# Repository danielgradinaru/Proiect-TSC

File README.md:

# eBook Reader

Proiect hardware complet pentru un eBook Reader portabil, cu consum redus de energie, afisaj E-Paper si conectivitate moderna, proiectat in jurul microcontrollerului ESP32-C6-WROOM-1-N8.

# Arhitectura Hardware

## Microcontroller

### ESP32-C6-WROOM-1-N8
- Core RISC-V
- Conectivitate: Wi-Fi 6, Bluetooth 5
- Criptografie hardware
- [Specificații oficiale](https://www.espressif.com/en/products/modules/esp32-c6)

### Memorie Flash externă
- **W25Q512JVEIQ** – 64MB, conectată prin SPI

### Interfețe disponibile
- I2C, SPI și GPIO dedicate componentelor externe

---

## Alimentare

### USB-C (PMF0501)
- Intrare de 5V din surse standard

### Protecție ESD (USBLC6-2SC6Y)
- Protecție bidirecțională pentru liniile USB

### Încărcător Li-Po (MCP73831)
- Circuit simplu de încărcare pentru o celulă Li-Po (max. 500mA)

### Baterie
- Li-Po 3.7V

### Regulator LDO (MCP1700-3302E)
- Reglează tensiunea la 3.3V pentru alimentarea majorității componentelor

---

## Afișaj E-Ink

### Conector MP1
- Compatibil cu ecrane E-Ink de 1.54", 200x200px

### Circuit de alimentare pentru afișaj
- Componente: Q3 (tranzistor), L1 (inductor), D2 (diodă)
- Rol: generare tensiune specifică pentru EPD

### Selector tip display (SJ1)
- Jumpere pentru alegerea tipului de ecran

### Interfață
- SPI + GPIO, conectat direct la ESP32-C6

---

## Memorie Externă

- **Card SD (U4)** – pentru stocarea fișierelor eBook (conectat prin SPI)
- **64MB NOR Flash (W25Q512JVEIQ)** – memorie extinsă pentru firmware, fonturi, imagini (conectată pe SPI dedicat)

---

## Senzori și Periferice

### BME688
- Senzor pentru temperatură, umiditate, presiune și compuși volatili (VOCs)
- Comunicație: I2C

### RTC – DS3231SN
- Modul de timp real de înaltă precizie
- Comunicație: I2C

### MAX17048G-T10
- Fuel gauge pentru monitorizarea nivelului bateriei
- Comunicație: I2C

### Butoane (BD5229)
- Butoane Reset și Boot
- Conectate pe pini GPIO configurabili

### Qwiic / Stemma QT (J5)
- Conector pentru extensii rapide I2C

---

## Conexiuni ESP32-C6 (pini utilizati)

| Componenta     | Interfata  | Pini ESP32-C6                      | Observatii                    |
|----------------|------------|------------------------------------|-------------------------------|
| SD Card        | SPI        | GPIO10, GPIO11, GPIO12, GPIO13     | Bus SPI pentru card SD        |
| NOR Flash      | SPI        | GPIO6, GPIO7, GPIO8, GPIO9         | Bus SPI separat               |
| E-Ink Display  | SPI + GPIO | GPIO18, GPIO19, GPIO20, GPIO21     | Control display si date       |
| BME688         | I2C        | GPIO1 (SDA), GPIO2 (SCL)           | Bus comun I2C                 |
| DS3231         | I2C        | GPIO1 (SDA), GPIO2 (SCL)           | Comun cu ceilalti senzori     |
| MAX17048       | I2C        | GPIO1 (SDA), GPIO2 (SCL)           | Comun cu ceilalti senzori     |
| Butoane        | GPIO       | GPIO0 (RST), GPIO3 (BOOT)          | Control de sistem             |
| Test Pads      | GPIO/UART  | GPIO17, GPIO22                     | Debug                         |
| Stemma/Qwiic   | I2C        | GPIO1 (SDA), GPIO2 (SCL)           | Extensii rapide               |

---

## Estimare consum de energie

| Modul                  | Consum mediu        |
|------------------------|---------------------|
| ESP32-C6 activ         | ~80-100 mA          |
| ESP32-C6 deep sleep    | ~10 uA              |
| E-Ink refresh          | ~25 mA (temporar)   |
| SD Card (idle/acces)   | ~2 mA / ~50 mA      |
| RTC + BME688 standby   | ~3-5 uA             |
| MAX17048               | ~3 uA               |

**Durata estimata cu baterie 500mAh:**

- Utilizare medie: ~15-20 ore
- Standby (deep sleep): pana la cateva saptamani

---

## Informatii suplimentare

### Structura hardware
- Utilizare medie: ~15-20 ore
- Standby (deep sleep): pana la cateva saptamani

- PCB proiectat cu atentie la separarea blocurilor: alimentare, MCU, afisaj, senzori
- Plan de masa comun, trasee protejate si optimizate
- Mufe si conectori accesibili extern (USB, butoane, afisaj)

### Randari 3D si carcasa

- Randari disponibile cu componentele plasate
- Proiect finalizat atat din punct de vedere al carcasei 3D cat si al PCB
- Dimensiuni compacte si aspect ergonomic

## Aplicatii posibile

- eBook Reader offline
- Afisaj pentru date locale (calendar, vreme)

## Bill of Materials

| Name          | Reference                                                                      | Technical Sheet                                                                                                                                                                       | Model Link                                                                                                             |
|:--------------|:-------------------------------------------------------------------------------|:--------------------------------------------------------------------------------------------------------------------------------------------------------------------------------------|:-----------------------------------------------------------------------------------------------------------------------|
| BOOT_BUTTON   | BUTTON_CUSYOMV1                                                                | [Datasheet](https://industry.panasonic.com/global/en/downloads?tab=catalog&small_g_cd=203&part_no=EVQPUJ02K)                                                                          | [3D Model](https://industry.panasonic.com/global/en/products/control/switch/light-touch/number/evqpuj02k)              |
| C1            | ESP32_WROVER_EAGLE-LTSPICE_CC0402                                              | [Datasheet](https://componentsearchengine.com/Datasheets/2/CC0402MRX5R5BB106.pdf)                                                                                                     | [3D Model](https://componentsearchengine.com/part-view/CC0402MRX5R5BB106/YAGEO)                                        |
| C1_BAT        | ESP32_WROVER_EAGLE-LTSPICE_CC0402                                              | [Datasheet](https://componentsearchengine.com/Datasheets/2/CC0402MRX5R5BB106.pdf)                                                                                                     | [3D Model](https://componentsearchengine.com/part-view/CC0402MRX5R5BB106/YAGEO)                                        |
| C1_BAT1       | EAGLE-LTSPICE_CC0402                                                           | [Datasheet](https://s3.amazonaws.com/snapeda/datasheet/CC0402DRNPO9BN5R1_Yageo.pdf)                                                                                                   | [3D Model](https://www.snapeda.com/parts/CC0402DRNPO9BN5R1/Yageo/view-part/?ref=dk&t=LTSPICE_CC0402&con_ref=None)      |
| C2_BAT1       | EAGLE-LTSPICE_CC0402                                                           | [Datasheet](https://s3.amazonaws.com/snapeda/datasheet/CC0402DRNPO9BN5R1_Yageo.pdf)                                                                                                   | [3D Model](https://www.snapeda.com/parts/CC0402DRNPO9BN5R1/Yageo/view-part/?ref=dk&t=LTSPICE_CC0402&con_ref=None)      |
| C1_BAT2       | EAGLE-LTSPICE_CC0402                                                           | [Datasheet](https://s3.amazonaws.com/snapeda/datasheet/CC0402DRNPO9BN5R1_Yageo.pdf)                                                                                                   | [3D Model](https://www.snapeda.com/parts/CC0402DRNPO9BN5R1/Yageo/view-part/?ref=dk&t=LTSPICE_CC0402&con_ref=None)      |
| C2            | ESP32_WROVER_EAGLE-LTSPICE_CC0402                                              | [Datasheet](https://componentsearchengine.com/Datasheets/2/CC0402MRX5R5BB106.pdf)                                                                                                     | [3D Model](https://componentsearchengine.com/part-view/CC0402MRX5R5BB106/YAGEO)                                        |
| C2_BAT        | ESP32_WROVER_EAGLE-LTSPICE_CC0402                                              | [Datasheet](https://componentsearchengine.com/Datasheets/2/CC0402MRX5R5BB106.pdf)                                                                                                     | [3D Model](https://componentsearchengine.com/part-view/CC0402MRX5R5BB106/YAGEO)                                        |
| C3            | RCL_CPOL-EUCT3528                                                              | [Datasheet](https://s3.amazonaws.com/snapeda/datasheet/TAJB475K025RNJ_AVX.pdf)                                                                                                        | [3D Model](https://www.snapeda.com/parts/TAJB475K025RNJ/AVX/view-part/?ref=dk&t=capacitor%203528&con_ref=None)         |
| C4            | ESP32_WROVER_EAGLE-LTSPICE_CC0402                                              | [Datasheet](https://componentsearchengine.com/Datasheets/2/CC0402MRX5R5BB106.pdf)                                                                                                     | [3D Model](https://componentsearchengine.com/part-view/CC0402MRX5R5BB106/YAGEO)                                        |
| C4_USB        | ESP32_WROVER_EAGLE-LTSPICE_CC0402                                              | [Datasheet](https://componentsearchengine.com/Datasheets/2/CC0402MRX5R5BB106.pdf)                                                                                                     | [3D Model](https://componentsearchengine.com/part-view/CC0402MRX5R5BB106/YAGEO)                                        |
| C5            | ESP32_WROVER_EAGLE-LTSPICE_CC0402                                              | [Datasheet](https://componentsearchengine.com/Datasheets/2/CC0402MRX5R5BB106.pdf)                                                                                                     | [3D Model](https://componentsearchengine.com/part-view/CC0402MRX5R5BB106/YAGEO)                                        |
| C5_USB        | ESP32_WROVER_EAGLE-LTSPICE_CC0402                                              | [Datasheet](https://componentsearchengine.com/Datasheets/2/CC0402MRX5R5BB106.pdf)                                                                                                     | [3D Model](https://componentsearchengine.com/part-view/CC0402MRX5R5BB106/YAGEO)                                        |
| C6            | ESP32_WROVER_EAGLE-LTSPICE_CC0402                                              | [Datasheet](https://componentsearchengine.com/Datasheets/2/CC0402MRX5R5BB106.pdf)                                                                                                     | [3D Model](https://componentsearchengine.com/part-view/CC0402MRX5R5BB106/YAGEO)                                        |
| C7            | ESP32_WROVER_EAGLE-LTSPICE_CC0402                                              | [Datasheet](https://componentsearchengine.com/Datasheets/2/CC0402MRX5R5BB106.pdf)                                                                                                     | [3D Model](https://componentsearchengine.com/part-view/CC0402MRX5R5BB106/YAGEO)                                        |
| C8            | ESP32_WROVER_EAGLE-LTSPICE_CC0402                                              | [Datasheet](https://componentsearchengine.com/Datasheets/2/CC0402MRX5R5BB106.pdf)                                                                                                     | [3D Model](https://componentsearchengine.com/part-view/CC0402MRX5R5BB106/YAGEO)                                        |
| C9            | EAGLE-LTSPICE_CC0402                                                           | [Datasheet](https://s3.amazonaws.com/snapeda/datasheet/CC0402DRNPO9BN5R1_Yageo.pdf)                                                                                                   | [3D Model](https://www.snapeda.com/parts/CC0402DRNPO9BN5R1/Yageo/view-part/?ref=dk&t=LTSPICE_CC0402&con_ref=None)      |
| C10           | ESP32_WROVER_EAGLE-LTSPICE_CC0402                                              | [Datasheet](https://componentsearchengine.com/Datasheets/2/CC0402MRX5R5BB106.pdf)                                                                                                     | [3D Model](https://componentsearchengine.com/part-view/CC0402MRX5R5BB106/YAGEO)                                        |
| C10_SUPERCAP  | CPH3225A                                                                       | [Datasheet](https://www.snapeda.com/parts/CPH3225A/Seiko%20Instruments/datasheet/)                                                                                                    | [3D Model](https://www.snapeda.com/parts/CPH3225A/Seiko+Instruments/view-part/?ref=eda)                                |
| CHANGE_BUTTON | BUTTON_CUSYOMV1                                                                | [Datasheet](https://industry.panasonic.com/global/en/downloads?tab=catalog&small_g_cd=203&part_no=EVQPUJ02K)                                                                          | [3D Model](https://industry.panasonic.com/global/en/products/control/switch/light-touch/number/evqpuj02k)              |
| CHG_LED       | ADAFRUIT_LEDCHIP-LED0603                                                       | [Datasheet](https://www.snapeda.com/parts/KP-1608SURCK/Kingbright/datasheet/)                                                                                                         | [3D Model](https://www.snapeda.com/parts/KP-1608SURCK/Kingbright/view-part/?ref=search&t=LED%200603)                   |
| C_DELAY       | ESP32_WROVER_EAGLE-LTSPICE_CC0402                                              | [Datasheet](https://componentsearchengine.com/Datasheets/2/CC0402MRX5R5BB106.pdf)                                                                                                     | [3D Model](https://componentsearchengine.com/part-view/CC0402MRX5R5BB106/YAGEO)                                        |
| D1            | USBLC6-2SC6Y                                                                   | [Datasheet](https://www.snapeda.com/parts/USBLC6-2SC6Y/STMicroelectronics/datasheet/)                                                                                                 | [3D Model](https://www.snapeda.com/parts/USBLC6-2SC6Y/STMicroelectronics/view-part/?ref=snap)                          |
| D2            | ESP32_WROVER_AVX---SD0805S020S1R0_AVX_SD0805S020S1R0_0_0AVX_SD0805S020S1R0_0_0 | [Datasheet](http://datasheets.avx.com/schottky.pdf)                                                                                                                                   | [3D Model](https://ro.mouser.com/ProductDetail/KYOCERA-AVX/SD0805S020S1R0?qs=jCA%252BPfw4LHbpkAoSnwrdjw%3D%3D)         |
| D3            | MBR0530                                                                        | [Datasheet](https://www.snapeda.com/parts/MBR0530/ON%20Semiconductor/datasheet/)                                                                                                      | [3D Model](https://www.snapeda.com/parts/MBR0530/Onsemi/view-part/?ref=eda)                                            |
| D4            | MBR0530                                                                        | [Datasheet](https://www.snapeda.com/parts/MBR0530/ON%20Semiconductor/datasheet/)                                                                                                      | [3D Model](https://www.snapeda.com/parts/MBR0530/Onsemi/view-part/?ref=eda)                                            |
| D5            | MBR0530                                                                        | [Datasheet](https://www.snapeda.com/parts/MBR0530/ON%20Semiconductor/datasheet/)                                                                                                      | [3D Model](https://www.snapeda.com/parts/MBR0530/Onsemi/view-part/?ref=eda)                                            |
| D6            | PGB1010603MR                                                                   | [Datasheet](https://www.snapeda.com/parts/PGB1010603MR/Littelfuse%20Inc./datasheet/)                                                                                                  | [3D Model](https://www.snapeda.com/parts/PGB1010603MR/Littelfuse/view-part/?ref=eda)                                   |
| D7            | ESP32_WROVER_AVX---SD0805S020S1R0_AVX_SD0805S020S1R0_0_0AVX_SD0805S020S1R0_0_0 | [Datasheet](http://datasheets.avx.com/schottky.pdf)                                                                                                                                   | [3D Model](https://eu.mouser.com/ProductDetail/KYOCERA-AVX/SD0805S020S1R0?qs=jCA%252BPfw4LHbpkAoSnwrdjw%3D%3D)         |
| D8            | PGB1010603MR                                                                   | [Datasheet](https://www.snapeda.com/parts/PGB1010603MR/Littelfuse%20Inc./datasheet/)                                                                                                  | [3D Model](https://www.snapeda.com/parts/PGB1010603MR/Littelfuse/view-part/?ref=eda)                                   |
| D9            | PGB1010603MR                                                                   | [Datasheet](https://www.snapeda.com/parts/PGB1010603MR/Littelfuse%20Inc./datasheet/)                                                                                                  | [3D Model](https://www.snapeda.com/parts/PGB1010603MR/Littelfuse/view-part/?ref=eda)                                   |
| D10           | PGB1010603MR                                                                   | [Datasheet](https://www.snapeda.com/parts/PGB1010603MR/Littelfuse%20Inc./datasheet/)                                                                                                  | [3D Model](https://www.snapeda.com/parts/PGB1010603MR/Littelfuse/view-part/?ref=eda)                                   |
| D11           | PGB1010603MR                                                                   | [Datasheet](https://www.snapeda.com/parts/PGB1010603MR/Littelfuse%20Inc./datasheet/)                                                                                                  | [3D Model](https://www.snapeda.com/parts/PGB1010603MR/Littelfuse/view-part/?ref=eda)                                   |
| D12           | PGB1010603MR                                                                   | [Datasheet](https://www.snapeda.com/parts/PGB1010603MR/Littelfuse%20Inc./datasheet/)                                                                                                  | [3D Model](https://www.snapeda.com/parts/PGB1010603MR/Littelfuse/view-part/?ref=eda)                                   |
| EPD_C1        | ESP32_WROVER_EAGLE-LTSPICE_CC0402                                              | [Datasheet](https://componentsearchengine.com/Datasheets/2/CC0402MRX5R5BB106.pdf)                                                                                                     | [3D Model](https://componentsearchengine.com/part-view/CC0402MRX5R5BB106/YAGEO)                                        |
| EPD_C2        | ESP32_WROVER_EAGLE-LTSPICE_CC0402                                              | [Datasheet](https://componentsearchengine.com/Datasheets/2/CC0402MRX5R5BB106.pdf)                                                                                                     | [3D Model](https://componentsearchengine.com/part-view/CC0402MRX5R5BB106/YAGEO)                                        |
| EPD_C5        | ESP32_WROVER_EAGLE-LTSPICE_CC0402                                              | [Datasheet](https://componentsearchengine.com/Datasheets/2/CC0402MRX5R5BB106.pdf)                                                                                                     | [3D Model](https://componentsearchengine.com/part-view/CC0402MRX5R5BB106/YAGEO)                                        |
| EPD_C6        | ESP32_WROVER_EAGLE-LTSPICE_CC0402                                              | [Datasheet](https://componentsearchengine.com/Datasheets/2/CC0402MRX5R5BB106.pdf)                                                                                                     | [3D Model](https://componentsearchengine.com/part-view/CC0402MRX5R5BB106/YAGEO)                                        |
| EPD_C7        | ESP32_WROVER_EAGLE-LTSPICE_CC0402                                              | [Datasheet](https://componentsearchengine.com/Datasheets/2/CC0402MRX5R5BB106.pdf)                                                                                                     | [3D Model](https://componentsearchengine.com/part-view/CC0402MRX5R5BB106/YAGEO)                                        |
| EPD_C8        | ESP32_WROVER_EAGLE-LTSPICE_CC0402                                              | [Datasheet](https://componentsearchengine.com/Datasheets/2/CC0402MRX5R5BB106.pdf)                                                                                                     | [3D Model](https://componentsearchengine.com/part-view/CC0402MRX5R5BB106/YAGEO)                                        |
| EPD_C9        | ESP32_WROVER_EAGLE-LTSPICE_CC0402                                              | [Datasheet](https://componentsearchengine.com/Datasheets/2/CC0402MRX5R5BB106.pdf)                                                                                                     | [3D Model](https://componentsearchengine.com/part-view/CC0402MRX5R5BB106/YAGEO)                                        |
| EPD_C10       | ESP32_WROVER_EAGLE-LTSPICE_CC0402                                              | [Datasheet](https://componentsearchengine.com/Datasheets/2/CC0402MRX5R5BB106.pdf)                                                                                                     | [3D Model](https://componentsearchengine.com/part-view/CC0402MRX5R5BB106/YAGEO)                                        |
| EPD_C11       | ESP32_WROVER_EAGLE-LTSPICE_CC0402                                              | [Datasheet](https://componentsearchengine.com/Datasheets/2/CC0402MRX5R5BB106.pdf)                                                                                                     | [3D Model](https://componentsearchengine.com/part-view/CC0402MRX5R5BB106/YAGEO)                                        |
| EPD_C12       | ESP32_WROVER_EAGLE-LTSPICE_CC0402                                              | [Datasheet](https://componentsearchengine.com/Datasheets/2/CC0402MRX5R5BB106.pdf)                                                                                                     | [3D Model](https://componentsearchengine.com/part-view/CC0402MRX5R5BB106/YAGEO)                                        |
| IC1           | BD5229G-TR                                                                     | [Datasheet](https://datasheet.datasheetarchive.com/originals/distributors/Datasheets_SAMA/f2b9741ef86007909f138d561a359946.pdf)                                                       | [3D Model](https://componentsearchengine.com/part-view/BD5229G-TR/ROHM%20Semiconductor)                                |
| IC4           | XC6220A331MR-G                                                                 | [Datasheet](https://product.torexsemi.com/system/files/series/xc6220.pdf)                                                                                                             | [3D Model](https://componentsearchengine.com/part-view/XC6220A331MR-G/Torex)                                           |
| J1            | FH34SRJ-24S-0.5SH_99_                                                          | [Datasheet](https://www.hirose.com/en/product/document?clcode=CL0580-1255-6-99&productname=FH34SRJ-24S-0.5SH(99)&series=FH34SRJ&documenttype=2DDrawing&lang=en&documentid=0000990903) | [3D Model](https://componentsearchengine.com/part-view/FH34SRJ-24S-0.5SH(99)/Hirose)                                   |
| J2            | SAMACSYS_PARTS_USB4110-GF-A                                                    | [Datasheet](https://gct.co/files/drawings/usb4110.pdf)                                                                                                                                | [3D Model](https://componentsearchengine.com/part-view/USB4110-GF-A/GCT%20(GLOBAL%20CONNECTOR%20TECHNOLOGY))           |
| J3            | QWIIC_CONNECTORJS-1MM                                                          | [Datasheet](https://eu.mouser.com/ProductDetail/Adafruit/4208?qs=PzGy0jfpSMtbScLbr0L5dw%3D%3D)                                                                                        | [3D Model](https://grabcad.com/library/sparkfun-qwiic-right-angle-1)                                                   |
| J4            | 112A-TAAR-R03_ATTEND                                                           | [Datasheet](https://store.comet.srl.ro/Catalogue/Product/43497/)                                                                                                                      | [3D Model](https://store.comet.srl.ro/Catalogue/Product/43497/)                                                        |
| L1            | 744043680IND_4828-WE-TPC_WRE                                                   | [Datasheet](https://www.we-online.com/components/products/datasheet/744043680.pdf)                                                                                                    | [3D Model](https://ro.mouser.com/ProductDetail/Wurth-Elektronik/744043680?qs=PGXP4M47uW6VkZq%252BkzjrHA%3D%3D)         |
| PFMF.050.1    | ESP32C6_VARISTORCN1812                                                         | [Datasheet](https://www.mouser.co.uk/ProductDetail/EPCOS-TDK/B72520T0350K062?qs=dEfas%2FXlABIszF52uu7vrg%3D%3D)                                                                       | [3D Model](https://www.mouser.co.uk/ProductDetail/EPCOS-TDK/B72520T0350K062?qs=dEfas%2FXlABIszF52uu7vrg%3D%3D)         |
| Q1            | ESP32_WROVER_SPARKFUN-DISCRETESEMI_MOSFET_PCH-DMG2305UX-7                      | [Datasheet](https://www.diodes.com//assets/Datasheets/DMG2305UX.pdf)                                                                                                                  | [3D Model](https://componentsearchengine.com/part-view/DMG2305UX-7/Diodes%20Incorporated)                              |
| Q2            | ESP32_WROVER_SPARKFUN-DISCRETESEMI_MOSFET_PCH-DMG2305UX-7                      | [Datasheet](https://www.diodes.com//assets/Datasheets/DMG2305UX.pdf)                                                                                                                  | [3D Model](https://componentsearchengine.com/part-view/DMG2305UX-7/Diodes%20Incorporated)                              |
| Q3            | D8                                                                             | [Datasheet](https://componentsearchengine.com/Datasheets/1/SI1308EDL-T1-GE3.pdf)                                                                                                      | [3D Model](https://componentsearchengine.com/part-view/SI1308EDL-T1-GE3/Vishay)                                        |
| R1            | ESP32_WROVER_EAGLE-LTSPICE_RR0402                                              | [Datasheet](https://www.yageo.com/upload/media/product/products/datasheet/rchip/PYu-RC_Group_51_RoHS_L_12.pdf)                                                                        | [3D Model](https://componentsearchengine.com/part-view/R0402%201%25%20100%20K%20(RC0402FR-07100KL)/YAGEO)              |
| R1-PINH       | ESP32_WROVER_EAGLE-LTSPICE_RR0402                                              | [Datasheet](https://www.yageo.com/upload/media/product/products/datasheet/rchip/PYu-RC_Group_51_RoHS_L_12.pdf)                                                                        | [3D Model](https://componentsearchengine.com/part-view/R0402%201%25%20100%20K%20(RC0402FR-07100KL)/YAGEO)              |
| R1-PINH1      | ESP32_WROVER_EAGLE-LTSPICE_RR0402                                              | [Datasheet](https://www.yageo.com/upload/media/product/products/datasheet/rchip/PYu-RC_Group_51_RoHS_L_12.pdf)                                                                        | [3D Model](https://componentsearchengine.com/part-view/R0402%201%25%20100%20K%20(RC0402FR-07100KL)/YAGEO)              |
| R1_BAT        | ESP32_WROVER_EAGLE-LTSPICE_RR0402                                              | [Datasheet](https://www.yageo.com/upload/media/product/products/datasheet/rchip/PYu-RC_Group_51_RoHS_L_12.pdf)                                                                        | [3D Model](https://componentsearchengine.com/part-view/R0402%201%25%20100%20K%20(RC0402FR-07100KL)/YAGEO)              |
| R1_PWRUSB     | ESP32_WROVER_EAGLE-LTSPICE_RR0402                                              | [Datasheet](https://www.yageo.com/upload/media/product/products/datasheet/rchip/PYu-RC_Group_51_RoHS_L_12.pdf)                                                                        | [3D Model](https://componentsearchengine.com/part-view/R0402%201%25%20100%20K%20(RC0402FR-07100KL)/YAGEO)              |
| R2            | ESP32_WROVER_EAGLE-LTSPICE_RR0402                                              | [Datasheet](https://www.yageo.com/upload/media/product/products/datasheet/rchip/PYu-RC_Group_51_RoHS_L_12.pdf)                                                                        | [3D Model](https://componentsearchengine.com/part-view/R0402%201%25%20100%20K%20(RC0402FR-07100KL)/YAGEO)              |
| R2-PINH       | ESP32_WROVER_EAGLE-LTSPICE_RR0402                                              | [Datasheet](https://www.yageo.com/upload/media/product/products/datasheet/rchip/PYu-RC_Group_51_RoHS_L_12.pdf)                                                                        | [3D Model](https://componentsearchengine.com/part-view/R0402%201%25%20100%20K%20(RC0402FR-07100KL)/YAGEO)              |
| R2-PINH1      | ESP32_WROVER_EAGLE-LTSPICE_RR0402                                              | [Datasheet](https://www.yageo.com/upload/media/product/products/datasheet/rchip/PYu-RC_Group_51_RoHS_L_12.pdf)                                                                        | [3D Model](https://componentsearchengine.com/part-view/R0402%201%25%20100%20K%20(RC0402FR-07100KL)/YAGEO)              |
| R2-USB        | ESP32_WROVER_EAGLE-LTSPICE_RR0402                                              | [Datasheet](https://www.yageo.com/upload/media/product/products/datasheet/rchip/PYu-RC_Group_51_RoHS_L_12.pdf)                                                                        | [3D Model](https://componentsearchengine.com/part-view/R0402%201%25%20100%20K%20(RC0402FR-07100KL)/YAGEO)              |
| R2-USB1       | ESP32_WROVER_EAGLE-LTSPICE_RR0402                                              | [Datasheet](https://www.yageo.com/upload/media/product/products/datasheet/rchip/PYu-RC_Group_51_RoHS_L_12.pdf)                                                                        | [3D Model](https://componentsearchengine.com/part-view/R0402%201%25%20100%20K%20(RC0402FR-07100KL)/YAGEO)              |
| R2_BAT        | ESP32_WROVER_EAGLE-LTSPICE_RR0402                                              | [Datasheet](https://www.yageo.com/upload/media/product/products/datasheet/rchip/PYu-RC_Group_51_RoHS_L_12.pdf)                                                                        | [3D Model](https://componentsearchengine.com/part-view/R0402%201%25%20100%20K%20(RC0402FR-07100KL)/YAGEO)              |
| R3            | ESP32_WROVER_EAGLE-LTSPICE_RR0402                                              | [Datasheet](https://www.yageo.com/upload/media/product/products/datasheet/rchip/PYu-RC_Group_51_RoHS_L_12.pdf)                                                                        | [3D Model](https://componentsearchengine.com/part-view/R0402%201%25%20100%20K%20(RC0402FR-07100KL)/YAGEO)              |
| R4            | ESP32_WROVER_EAGLE-LTSPICE_RR0402                                              | [Datasheet](https://www.yageo.com/upload/media/product/products/datasheet/rchip/PYu-RC_Group_51_RoHS_L_12.pdf)                                                                        | [3D Model](https://componentsearchengine.com/part-view/R0402%201%25%20100%20K%20(RC0402FR-07100KL)/YAGEO)              |
| R5            | ESP32_WROVER_EAGLE-LTSPICE_RR0402                                              | [Datasheet](https://www.yageo.com/upload/media/product/products/datasheet/rchip/PYu-RC_Group_51_RoHS_L_12.pdf)                                                                        | [3D Model](https://componentsearchengine.com/part-view/R0402%201%25%20100%20K%20(RC0402FR-07100KL)/YAGEO)              |
| R6            | ESP32_WROVER_EAGLE-LTSPICE_RR0402                                              | [Datasheet](https://www.yageo.com/upload/media/product/products/datasheet/rchip/PYu-RC_Group_51_RoHS_L_12.pdf)                                                                        | [3D Model](https://componentsearchengine.com/part-view/R0402%201%25%20100%20K%20(RC0402FR-07100KL)/YAGEO)              |
| R7            | ESP32_WROVER_EAGLE-LTSPICE_RR0402                                              | [Datasheet](https://www.yageo.com/upload/media/product/products/datasheet/rchip/PYu-RC_Group_51_RoHS_L_12.pdf)                                                                        | [3D Model](https://componentsearchengine.com/part-view/R0402%201%25%20100%20K%20(RC0402FR-07100KL)/YAGEO)              |
| R8            | ESP32_WROVER_EAGLE-LTSPICE_RR0402                                              | [Datasheet](https://www.yageo.com/upload/media/product/products/datasheet/rchip/PYu-RC_Group_51_RoHS_L_12.pdf)                                                                        | [3D Model](https://componentsearchengine.com/part-view/R0402%201%25%20100%20K%20(RC0402FR-07100KL)/YAGEO)              |
| R9            | ESP32_WROVER_EAGLE-LTSPICE_RR0402                                              | [Datasheet](https://www.yageo.com/upload/media/product/products/datasheet/rchip/PYu-RC_Group_51_RoHS_L_12.pdf)                                                                        | [3D Model](https://componentsearchengine.com/part-view/R0402%201%25%20100%20K%20(RC0402FR-07100KL)/YAGEO)              |
| R10           | ESP32_WROVER_EAGLE-LTSPICE_RR0402                                              | [Datasheet](https://www.yageo.com/upload/media/product/products/datasheet/rchip/PYu-RC_Group_51_RoHS_L_12.pdf)                                                                        | [3D Model](https://componentsearchengine.com/part-view/R0402%201%25%20100%20K%20(RC0402FR-07100KL)/YAGEO)              |
| RESET_BUTTON  | BUTTON_CUSYOMV1                                                                | [Datasheet](https://industry.panasonic.com/global/en/downloads?tab=catalog&small_g_cd=203&part_no=EVQPUJ02K)                                                                          | [3D Model](https://industry.panasonic.com/global/en/products/control/switch/light-touch/number/evqpuj02k)              |
| R_BOOT        | ESP32_WROVER_EAGLE-LTSPICE_RR0402                                              | [Datasheet](https://www.yageo.com/upload/media/product/products/datasheet/rchip/PYu-RC_Group_51_RoHS_L_12.pdf)                                                                        | [3D Model](https://componentsearchengine.com/part-view/R0402%201%25%20100%20K%20(RC0402FR-07100KL)/YAGEO)              |
| R_CAPACITOR   | ESP32_WROVER_EAGLE-LTSPICE_RR0402                                              | [Datasheet](https://www.yageo.com/upload/media/product/products/datasheet/rchip/PYu-RC_Group_51_RoHS_L_12.pdf)                                                                        | [3D Model](https://componentsearchengine.com/part-view/R0402%201%25%20100%20K%20(RC0402FR-07100KL)/YAGEO)              |
| R_CHANGE      | ESP32_WROVER_EAGLE-LTSPICE_RR0402                                              | [Datasheet](https://www.yageo.com/upload/media/product/products/datasheet/rchip/PYu-RC_Group_51_RoHS_L_12.pdf)                                                                        | [3D Model](https://componentsearchengine.com/part-view/R0402%201%25%20100%20K%20(RC0402FR-07100KL)/YAGEO)              |
| R_CL1         | ESP32_WROVER_EAGLE-LTSPICE_RR0402                                              | [Datasheet](https://www.yageo.com/upload/media/product/products/datasheet/rchip/PYu-RC_Group_51_RoHS_L_12.pdf)                                                                        | [3D Model](https://componentsearchengine.com/part-view/R0402%201%25%20100%20K%20(RC0402FR-07100KL)/YAGEO)              |
| R_RESET       | ESP32_WROVER_EAGLE-LTSPICE_RR0402                                              | [Datasheet](https://www.yageo.com/upload/media/product/products/datasheet/rchip/PYu-RC_Group_51_RoHS_L_12.pdf)                                                                        | [3D Model](https://componentsearchengine.com/part-view/R0402%201%25%20100%20K%20(RC0402FR-07100KL)/YAGEO)              |
| SENSOR2       | ESP32_WROVER_BME680_BME680                                                     | [Datasheet](https://www.snapeda.com/parts/BME680/Bosch%20Sensortec/datasheet/)                                                                                                        | [3D Model](https://www.snapeda.com/parts/BME680/Bosch/view-part/?welcome=home)                                         |
| SJ1           | SJ                                                                             | [Datasheet](https://www.digikey.com/en/htmldatasheets/production/1809569/0/0/1/jumpers)                                                                                               | [3D Model](https://grabcad.com/library/solder-jumpers-1)                                                               |
| U1            | W25Q512JVEIQ                                                                   | [Datasheet](https://www.snapeda.com/parts/W25Q512JVEIQ/Winbond%20Electronics/datasheet/)                                                                                              | [3D Model](https://www.snapeda.com/parts/W25Q512JVEIQ/Winbond+Electronics/view-part/?ref=eda)                          |
| U2            | ESP32-C6-WROOM-1-N8                                                            | [Datasheet](https://www.snapeda.com/parts/ESP32-C6-WROOM-1-N8/Espressif%20Systems/datasheet/)                                                                                         | [3D Model](https://www.snapeda.com/parts/ESP32-C6-WROOM-1-N8/Espressif+Systems/view-part/?ref=eda)                     |
| U3            | DS3231SN#                                                                      | [Datasheet](https://www.snapeda.com/parts/DS3231SN%23/Analog%20Devices/datasheet/)                                                                                                    | [3D Model](https://www.snapeda.com/parts/DS3231SN%23/Analog+Devices/view-part/?ref=eda)                                |
| U4            | MAX17048G+T10                                                                  | [Datasheet](https://www.snapeda.com/parts/MAX17048G+T10/Analog%20Devices/datasheet/)                                                                                                  | [3D Model](https://www.snapeda.com/parts/MAX17048G+T10/Analog+Devices/view-part/?ref=eda)                              |
| U5            | ESP32_WROVER_SPARKFUN-IC-POWER_MCP73831                                        | [Datasheet](https://ro.mouser.com/datasheet/2/268/MCP73831_Family_Data_Sheet_DS20001984H-3441711.pdf)                                                                                 | [3D Model](https://ro.mouser.com/ProductDetail/Microchip-Technology/MCP73831T-2ACI-OT?qs=yUQqVecv4qvbBQBGbHx0Mw%3D%3D) |
| TP1           | TPTP20R                                                                        |                                                                                                                                                                                       |                                                                                                                        |
| TP2           | TPTP20R                                                                        |                                                                                                                                                                                       |                                                                                                                        |
| TP3           | TPTP20R                                                                        |                                                                                                                                                                                       |                                                                                                                        |
| TP4           | TPTP20R                                                                        |                                                                                                                                                                                       |                                                                                                                        |
| TP5           | TPTP20R                                                                        |                                                                                                                                                                                       |                                                                                                                        |
| TP6           | TPTP20R                                                                        |                                                                                                                                                                                       |                                                                                                                        |
| TP7           | TPTP20R                                                                        |                                                                                                                                                                                       |                                                                                                                        |
| TP8           | TPTP20R                                                                        |                                                                                                                                                                                       |                                                                                                                        |
| TP9           | TPTP20R                                                                        |                                                                                                                                                                                       |                                                                                                                        |
| TP10          | TPTP20R                                                                        |                                                                                                                                                                                       |                                                                                                                        |
| TP11          | TPTP20R                                                                        |                                                                                                                                                                                       |                                                                                                                        |
| TP12          | TPTP20R                                                                        |                                                                                                                                                                                       |                                                                                                                        |
| TP13          | TPTP20R                                                                        |                                                                                                                                                                                       |                                                                                                                        |
| TP14          | TPTP20R                                                                        |                                                                                                                                                                                       |                                                                                                                        |
| TP15          | TPTP20R                                                                        |                                                                                                                                                                                       |                                                                                                                        |
| TP16          | TPTP20R                                                                        |                                                                                                                                                                                       |                                                                                                                        |

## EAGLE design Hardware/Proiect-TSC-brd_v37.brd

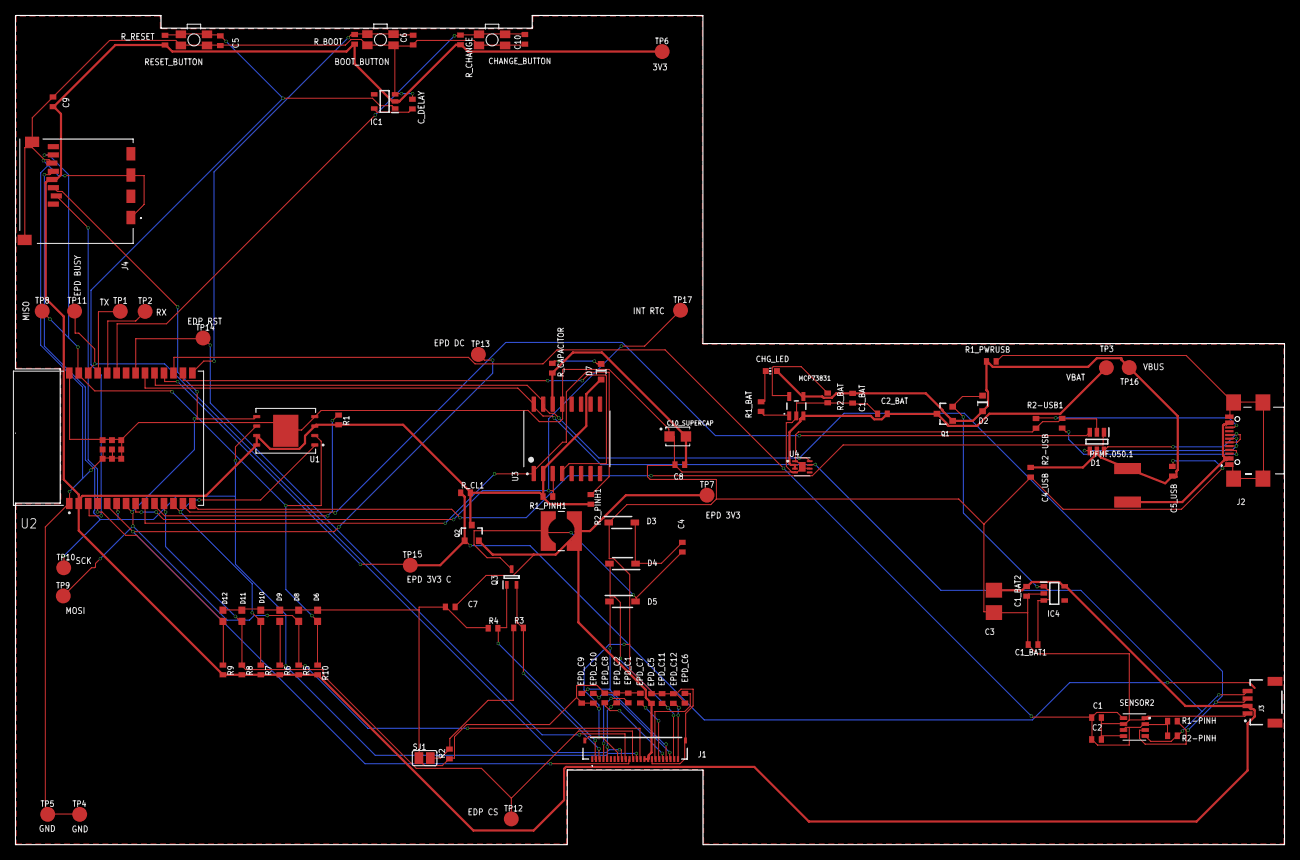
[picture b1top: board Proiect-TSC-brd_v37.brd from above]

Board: 2 copper layers, 170.2 x 111.2 mm, 103 parts (0 on the bottom side), 55 nets.

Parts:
BOOT_BUTTON: BUTTON_CUSYOMV1; MYBUTTON
C1, C2, C4_USB, C6, C8, C9, C10: 100nF; EAGLE-LTSPICE_C0402
C1_BAT, C1_BAT2, C2_BAT, C5_USB: 4.7uF; EAGLE-LTSPICE_C0402
C1_BAT1: 4.7uF; ESP32_WROVER_EAGLE-LTSPICE_C0402
C3: 100uF; RCL_CT3528
C4: 4.7uF/25V; EAGLE-LTSPICE_C0402
C5: 1uF; EAGLE-LTSPICE_C0402
C7: 10uF; EAGLE-LTSPICE_C0402
C10_SUPERCAP: CPH3225A; CAPCP3225X100N
CHANGE_BUTTON: BUTTON_CUSYOMV1; MYBUTTON
CHG_LED: ADAFRUIT_CHIP-LED0603
C_DELAY: 100nF; EAGLE-LTSPICE_C0402
D1: USBLC6-2SC6Y; SOT95P280X145-6N
D2, D7: ESP32_WROVER_AVX---SD0805S020S1R0_AVX_SD0805S020S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; ESP32_WROVER_AVX---SD0805S020S1R0_AVX_SD0805S020S1R0_0
D3, D4, D5: MBR0530; SOD3716X135N
D6, D8, D9, D10, D11, D12: PGB1010603MR; DIOC1608X36N
EPD_C1, EPD_C2, EPD_C5, EPD_C6, EPD_C7, EPD_C8, EPD_C9, EPD_C10, EPD_C11, EPD_C12: 1uF/50V; EAGLE-LTSPICE_C0402
IC1: BD5229G-TR; SOT95P280X125-5N
IC4: XC6220A331MR-G; SOT95P280X120-5N
J1: FH34SRJ-24S-0.5SH_99_; FH34SRJ24S05SH99
J2: SAMACSYS_PARTS_USB4110-GF-A; SAMACSYS_PARTS_USB4110GFA
J3: QWIIC_RIGHT_ANGLE; JST04_1MM_RA
J4: 112A-TAAR-R03_ATTEND; 112ATAARR03ATTEND
L1: 68uH; IND_4828-WE-TPC_WRE
MCP73831: ESP32_WROVER_SPARKFUN-IC-POWER_MCP73831; ESP32_WROVER_SPARKFUN-IC-POWER_SOT23-5
PFMF.050.1: ESP32C6_VARISTORCN1812; ESP32C6_VARISTOR_CT/CN1812
Q1, Q2: 20V/4.2A/52mΩ/1.4W; ESP32_WROVER_SPARKFUN-DISCRETESEMI_SOT23-3
Q3: SI1308EDL-T1-GE3; SOT65P210X110-3N
R1, R1-PINH, R1_PINH1, R2-PINH, R2_PINH1, R4, R5, R6, R7, R8, R9, R10: 10K; ESP32_WROVER_EAGLE-LTSPICE_R0402
R1_BAT: 200; ESP32_WROVER_EAGLE-LTSPICE_R0402
R1_PWRUSB: 100K; ESP32_WROVER_EAGLE-LTSPICE_R0402
R2: 2.2; ESP32_WROVER_EAGLE-LTSPICE_R0402
R2-USB: 5k1; ESP32_WROVER_EAGLE-LTSPICE_R0402
R2-USB1: 5K1; ESP32_WROVER_EAGLE-LTSPICE_R0402
R2_BAT: 2K; ESP32_WROVER_EAGLE-LTSPICE_R0402
R3: 0.47; ESP32_WROVER_EAGLE-LTSPICE_R0402
RESET_BUTTON: BUTTON_CUSYOMV1; MYBUTTON
R_BOOT: 10K; ESP32_WROVER_EAGLE-LTSPICE_R0402
R_CAPACITOR: 15; ESP32_WROVER_EAGLE-LTSPICE_R0402
R_CHANGE: 10K; ESP32_WROVER_EAGLE-LTSPICE_R0402
R_CL1: 10K; ESP32_WROVER_EAGLE-LTSPICE_R0402
R_RESET: 10K; ESP32_WROVER_EAGLE-LTSPICE_R0402
SENSOR2: BME688; ESP32_WROVER_BME680_PSON80P300X300X100-8N
SJ1: SJ
TP1, TP2, TP3, TP4, TP5, TP6, TP7, TP8, TP9, TP10, TP11, TP12, TP13, TP14, TP15, TP16, TP17: TPTP20R; TP20R
U1: W25Q512JVEIQ; SON127P600X800X80-9N
U2: ESP32-C6-WROOM-1-N8; XCVR_ESP32-C6-WROOM-1-N8
U3: DS3231SN#; SOIC127P1032X265-16N
U4: MAX17048G+T10; SON50P200X200X80-9N

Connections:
3V3: C1_BAT2.1, C3.+, C9.2, D7.2, IC1.2, IC4.5, J3.2, J4.P4, Q2.3, R1.2, R1_PINH1.2, R2_PINH1.2, R5.2, R6.2, R7.2, R8.2, R9.2, R10.2, R_BOOT.2, R_CHANGE.2, R_CL1.2, R_RESET.2, TP6.TP, U1.3, U1.7, U1.8, U2.2, U3.2
32KHZ: R2_PINH1.1, U2.9, U3.1
DN: D1.4, J2.A7, J2.B7
DP: D1.6, J2.A6, J2.B6
EPD_3V3: C7.1, EPD_C5.2, J1.15, J1.16, L1.2, Q2.2, TP7.TP
EPD_3V3_C: Q2.1, R_CL1.1, TP15.TP, U2.18
EPD_BUSY: J1.9, TP11.TP, U2.26
EPD_CS: D11.2, J1.12, R8.1, TP12.TP, U2.11
EPD_DC: J1.11, TP13.TP, U2.5
EPD_RST: J1.10, TP14.TP, U2.21
FLASH_CS: D10.2, R7.1, U1.1, U2.12
GDR: J1.2, Q3.1, R4.2
GND: BOOT_BUTTON.1, BOOT_BUTTON.2, C1.2, C1_BAT.2, C1_BAT1.2, C1_BAT2.2, C2.2, C2_BAT.2, C3.-, C4_USB.2, C5.2, C5_USB.2, C6.2, C7.2, C8.2, C9.1, C10.2, C10_SUPERCAP.1, CHANGE_BUTTON.1, CHANGE_BUTTON.2, C_DELAY.2, D1.2, D3.1, D6.1, D8.1, D9.1, D10.1, D11.1, D12.1, EPD_C1.1, EPD_C2.1, EPD_C5.1, EPD_C6.1, EPD_C7.1, EPD_C8.1, EPD_C9.1, EPD_C10.1, EPD_C11.1, EPD_C12.1, IC1.3, IC4.2, J1.8, J1.17, J1.MP1, J1.MP2, J2.A1, J2.A12, J2.B1, J2.B12, J2.MP1, J2.MP2, J2.MP3, J2.MP4, J3.1, J4.G1, J4.G2, J4.G3, J4.G4, J4.P6, MCP73831.2, R1_PWRUSB.1, R2.1, R2-USB.2, R2-USB1.1, R2_BAT.1, R4.1, RESET_BUTTON.1, RESET_BUTTON.2, SENSOR2.1, SENSOR2.5, SENSOR2.7, SJ1.1, TP4.TP, TP5.TP, U1.4, U1.9, U2.1, U2.28, U2.29_1, U2.29_2, U2.29_3, U2.29_4, U2.29_5, U2.29_6, U2.29_7, U2.29_8, U2.29_9, U3.13, U4.1, U4.4, U4.6, U4.9
GPIO8: R1.1, U2.10
I2C_PW: C1.1, C2.1, R1-PINH.2, R2-PINH.2, SENSOR2.2, SENSOR2.6, SENSOR2.8, U2.17
INT_RTC: R1_PINH1.1, TP17.TP, U2.8, U3.3
IO/BOOT: BOOT_BUTTON.3, BOOT_BUTTON.4, C6.1, R_BOOT.1, U2.15
IO/CHANGE: C10.1, CHANGE_BUTTON.3, CHANGE_BUTTON.4, R_CHANGE.1, U2.23
MISO: D6.2, J4.P7, R10.1, TP8.TP, U1.2, U2.27
MOSI: D8.2, J1.14, J4.P3, R5.1, TP9.TP, U1.5, U2.7
unnamed: J2.A5, R2-USB1.2
unnamed: J2.B5, R2-USB.1
unnamed: C_DELAY.1, IC1.5
unnamed: MCP73831.1, R1_BAT.2
unnamed: C1_BAT1.1, D2.1, IC4.1, IC4.3, Q1.2
unnamed: C4.1, D3.2, D4.1
unnamed: CHG_LED.C, R1_BAT.1
unnamed: MCP73831.5, R2_BAT.2
unnamed: EPD_C12.2, J1.24
unnamed: EPD_C10.2, J1.22
unnamed: EPD_C8.2, J1.20
unnamed: EPD_C7.2, J1.19
unnamed: EPD_C6.2, J1.18
unnamed: EPD_C2.2, J1.5
unnamed: EPD_C1.2, J1.4
unnamed: D7.1, R_CAPACITOR.1
PREVGH: D5.1, EPD_C9.2, J1.21
PREVGL: D4.2, EPD_C11.2, J1.23
RESE: J1.3, Q3.2, R3.2
RESE': R2.2, R3.1, SJ1.2
RESET: C5.1, IC1.1, RESET_BUTTON.3, RESET_BUTTON.4, R_RESET.1, U2.3
RTC_RST: U2.16, U3.4
RX: TP2.TP, U2.24
SCK: D9.2, J1.13, J4.P5, R6.1, TP10.TP, U1.6, U2.6
SCL: J3.4, R2-PINH.1, SENSOR2.4, U2.20, U3.16, U4.7
SDA: J3.3, R1-PINH.1, SENSOR2.3, U2.19, U3.15, U4.8
SRC: C4.2, D5.2, L1.1, Q3.3
SS_SD: D12.2, J4.P2, R9.1, U2.4
TX: TP1.TP, U2.25
USB_D+: D1.1, U2.14
USB_D-: D1.3, U2.13
VBAT: C2_BAT.1, MCP73831.3, Q1.3, TP3.TP, U4.2, U4.3
VBUS: C1_BAT.1, C4_USB.1, C5_USB.1, CHG_LED.A, D1.5, D2.2, MCP73831.4, PFMF.050.1.2, Q1.1, R1_PWRUSB.2, TP16.TP
VRTC: C8.1, C10_SUPERCAP.2, R_CAPACITOR.2, U3.14
VUSB: J2.A4, J2.A9, J2.B4, J2.B9, PFMF.050.1.1

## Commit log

2025-04-14 Create Images
2025-04-14 Issues solved

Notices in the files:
parts and their libraries:
COPYRIGHT: Copyright (C) 2024 Ultra Librarian. All rights reserved.
